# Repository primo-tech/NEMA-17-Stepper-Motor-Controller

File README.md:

# NEMA-17-Stepper-Motor-Controller
STM32L011F4P Based Closed-Loop Controller for NEMA-17 Stepper Motors

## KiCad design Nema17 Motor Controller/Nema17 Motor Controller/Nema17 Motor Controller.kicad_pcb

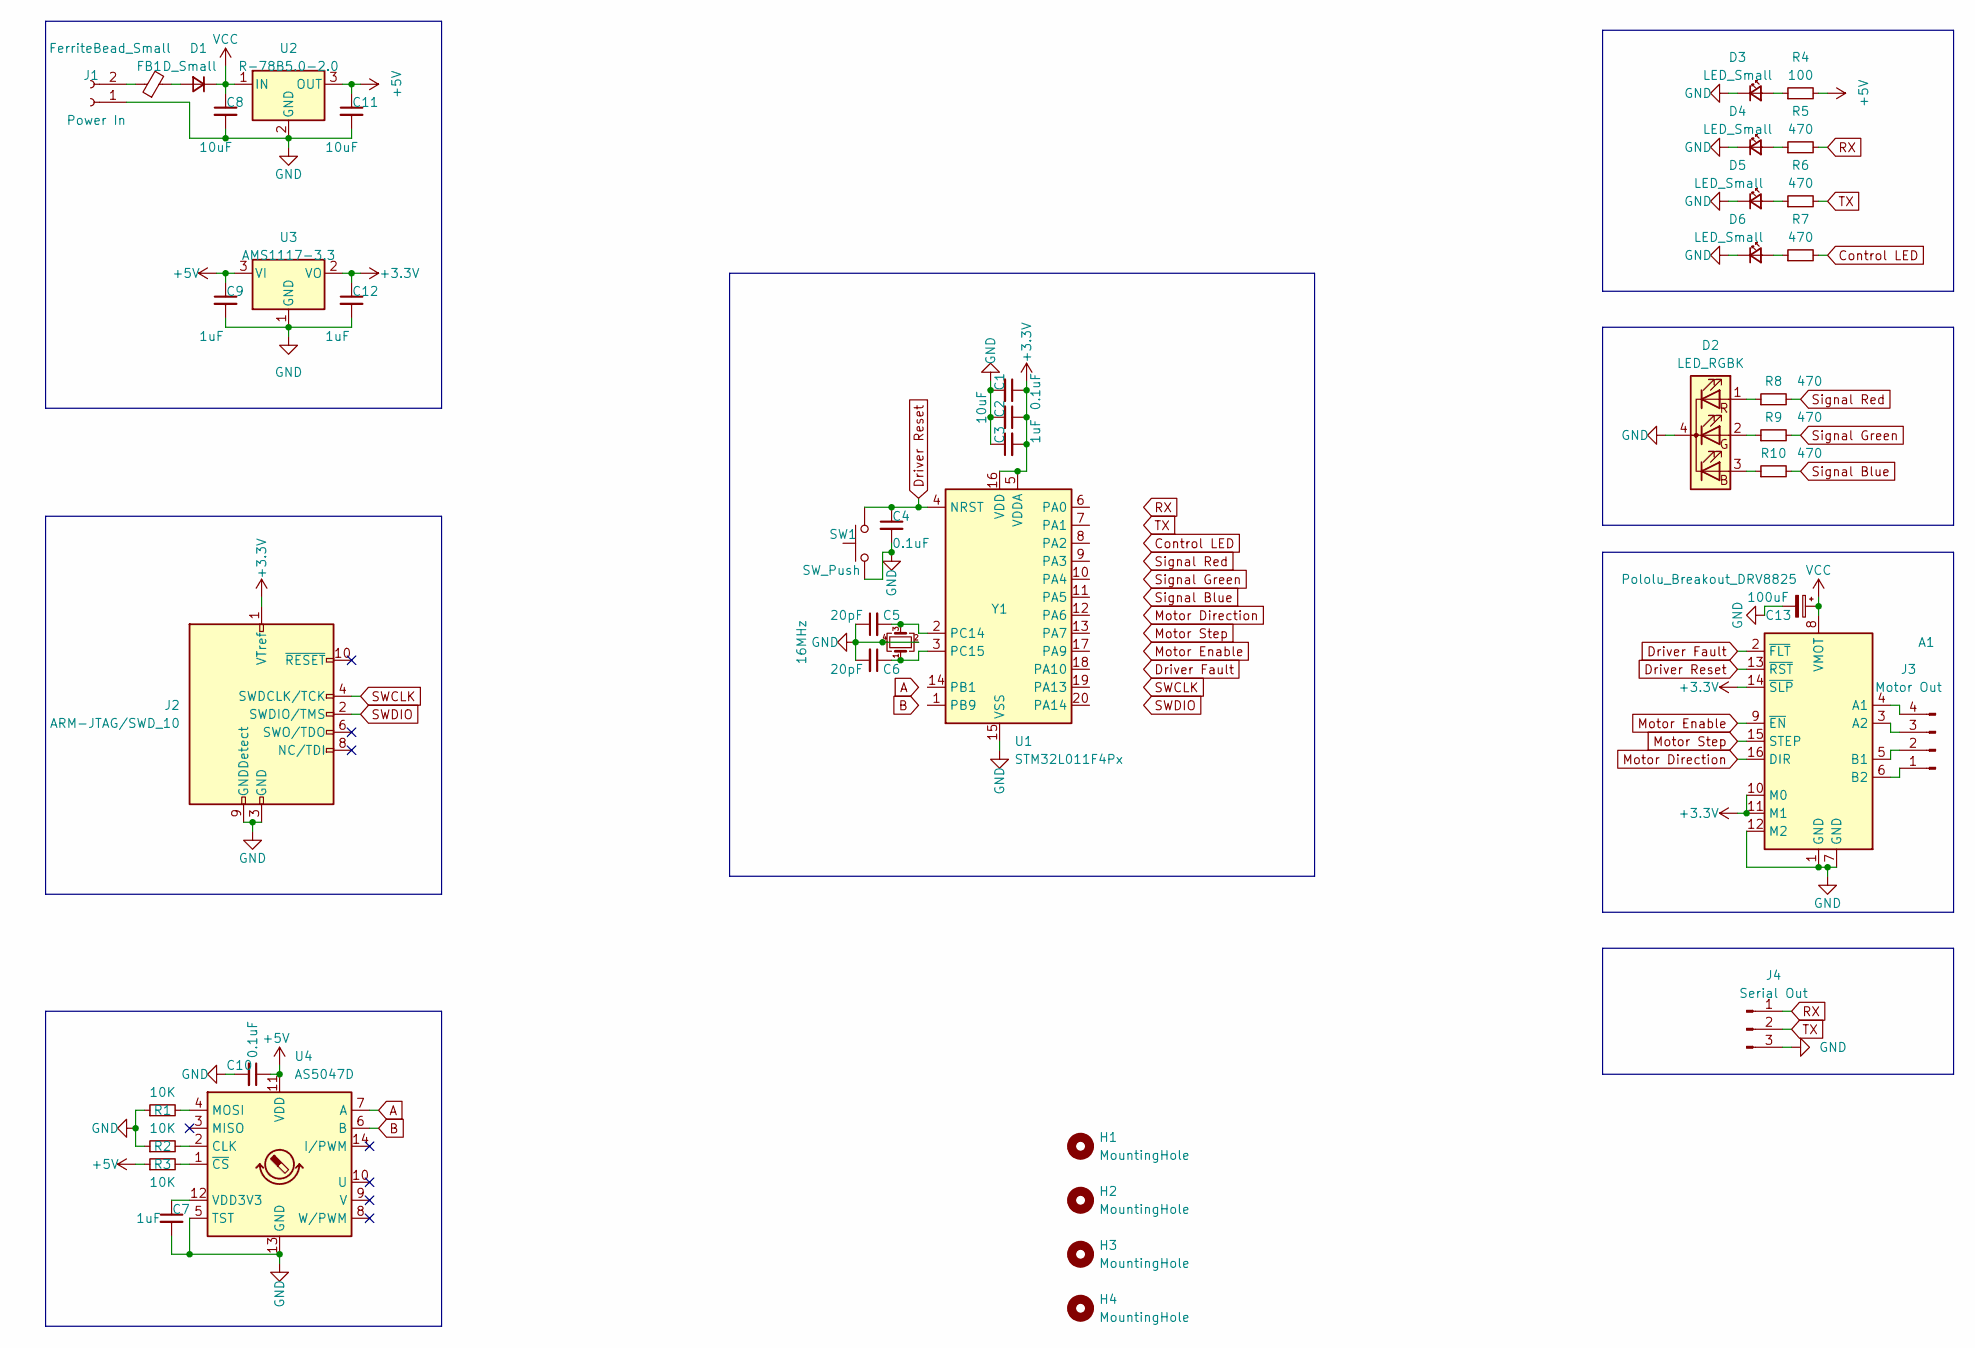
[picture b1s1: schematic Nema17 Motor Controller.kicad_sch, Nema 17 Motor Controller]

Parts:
A1: Pololu_Breakout_DRV8825; Pololu_Breakout-16_15.2x20.3mm
C1, C4, C10: 0.1uF; C_0805_2012Metric_Pad1.18x1.45mm_HandSolder
C2, C8, C11: 10uF; C_0805_2012Metric_Pad1.18x1.45mm_HandSolder
C3, C7, C9, C12: 1uF; C_0805_2012Metric_Pad1.18x1.45mm_HandSolder
C5, C6: 20pF; C_0805_2012Metric_Pad1.18x1.45mm_HandSolder
C13: 100uF; CP_Elec_6.3x3
D1: D_Small; D_0805_2012Metric_Pad1.15x1.40mm_HandSolder
D2: LED_RGBK; LED_RGB_1210
D3, D4, D5, D6: LED_Small; LED_0805_2012Metric_Pad1.15x1.40mm_HandSolder
FB1: FerriteBead_Small; L_0805_2012Metric_Pad1.15x1.40mm_HandSolder
H1, H2, H3, H4: MountingHole; MountingHole_3.2mm_M3
J1: Power In; PinHeader_1x02_P2.54mm_Horizontal
J2: ARM-JTAG/SWD_10; PinHeader_2x05_P2.54mm_Horizontal
J3: Motor Out; PinHeader_1x04_P2.54mm_Horizontal
J4: Serial Out; PinHeader_1x03_P2.54mm_Horizontal
R1, R2, R3: 10K; R_0805_2012Metric_Pad1.20x1.40mm_HandSolder
R4: 100; R_0805_2012Metric_Pad1.20x1.40mm_HandSolder
R5, R6, R7, R8, R9, R10: 470; R_0805_2012Metric_Pad1.20x1.40mm_HandSolder
SW1: SW_Push; SW_Push_1P1T_NO_6x6mm_H9.5mm
U1: STM32L011F4Px; TSSOP-20_4.4x6.5mm_P0.65mm
U2: R-78B5.0-2.0; Converter_DCDC_RECOM_R-78B-2.0_THT
U3: AMS1117-3.3; SOT-223-3_TabPin2
U4: AS5047D; TSSOP-14_4.4x5mm_P0.65mm
Y1: 16MHz; Crystal_SMD_Abracon_ABM8G-4Pin_3.2x2.5mm

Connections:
+3V3: A1.10 (M0), A1.11 (M1), A1.14 (~SLP), C1.1, C2.1, C3.2, C12.1, J2.1 (VTref), U1.5 (VDDA), U1.16 (VDD), U3.2 (VO)
+5V: C9.1, C10.1, C11.1, R3.1, R4.2, U2.3 (OUT), U3.3 (VI), U4.11 (VDD)
A: U4.7 (A)
B: U4.6 (B)
Control LED: R7.2
Driver Fault: A1.2 (~FLT)
Driver Reset: A1.13 (~RST), C4.1, SW1.2, U1.4 (NRST)
GND: A1.1 (GND), A1.7 (GND), A1.12 (M2), C1.2, C2.2, C3.1, C4.2, C5.1, C6.2, C7.2, C8.2, C9.2, C10.2, C11.2, C12.2, D2.4 (K), D3.1 (K), D4.1 (K), D5.1 (K), D6.1 (K), J1.1, J2.3 (GND), J2.5 (GND), J2.9 (GNDDetect), J4.3, R1.1, R2.1, SW1.1, U1.15 (VSS), U2.2 (GND), U3.1 (GND), U4.5 (TST), U4.13 (GND), Y1.2, Y1.4
Motor Direction: A1.16 (DIR)
Motor Enable: A1.9 (~EN)
Motor Step: A1.15 (STEP)
unnamed: A1.3 (A2), J3.3
unnamed: A1.4 (A1), J3.4
unnamed: A1.5 (B1), J3.2
unnamed: A1.6 (B2), J3.1
unnamed: C5.2, U1.2 (PC14), Y1.3
unnamed: C6.1, U1.3 (PC15), Y1.1
unnamed: D1.2 (A), FB1.2
unnamed: D2.1 (RA), R8.1
unnamed: D2.2 (GA), R9.1
unnamed: D2.3 (BA), R10.1
unnamed: D3.2 (A), R4.1
unnamed: D4.2 (A), R5.1
unnamed: D5.2 (A), R6.1
unnamed: D6.2 (A), R7.1
unnamed: FB1.1, J1.2
unnamed: R3.2, U4.1 (~CS)
unnamed: R2.2, U4.2 (CLK)
unnamed: R1.2, U4.4 (MOSI)
unnamed: C7.1, U4.12 (VDD3V3)
RX: J4.1, R5.2
SWCLK: J2.4 (SWDCLK/TCK)
SWDIO: J2.2 (SWDIO/TMS)
Signal Blue: R10.2
Signal Green: R9.2
Signal Red: R8.2
TX: J4.2, R6.2

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
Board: 2 copper layers, 45 parts (0 on the bottom side), 27 nets, no tracks yet.

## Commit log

2022-01-16 Firmware
2022-01-23 update
    pcb design continued, Motor control for position velocity and acceleration
